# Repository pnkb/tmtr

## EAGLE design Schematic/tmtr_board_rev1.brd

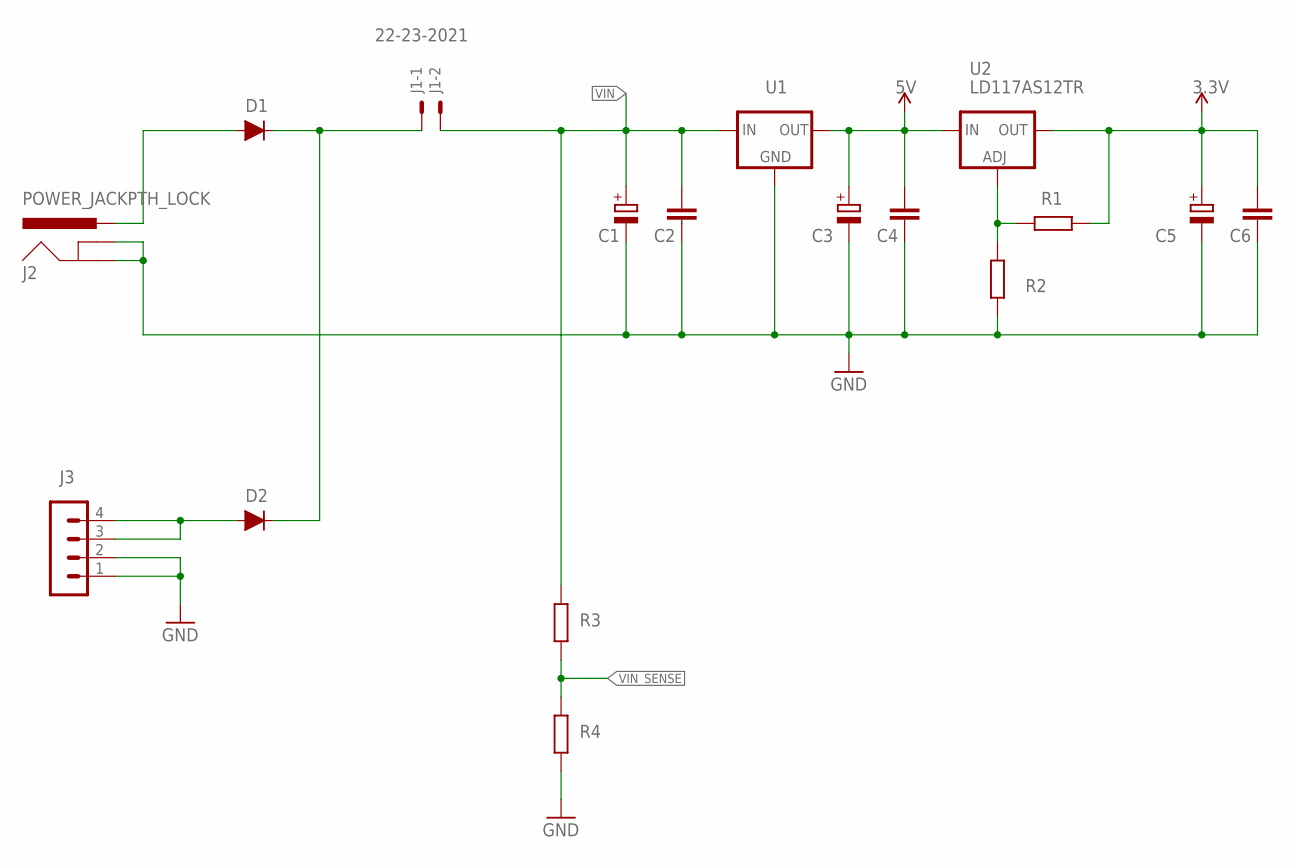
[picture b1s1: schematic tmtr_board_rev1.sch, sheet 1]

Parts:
C1: CPOL-EUE5-6; E5-6
C2, C4, C6: CAPPTH; CAP-PTH-SMALL
C3, C5: CPOL-EUE2.5-6; E2,5-6
D1, D2: D-FILL-SMB; SMB
J1: 22-23-2021
J2: POWER_JACKPTH_LOCK; POWER_JACK_PTH_LOCK
J3: MA04-1
R1, R2, R3, R4: R-EU_M0805; M0805
U1: 78XXS
U2: LD117AS12TR; SOT223

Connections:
3.3V: C5.+, C6.2, R1.2, U2.4 (OUT); also elsewhere on the board
5V: C3.+, C4.2, U1.OUT, U2.3 (IN); also elsewhere on the board
GND: C1.-, C2.1, C3.-, C4.1, C5.-, C6.1, J2.GND, J2.GNDBREAK, J3.1, J3.2, R2.2, R4.2, U1.GND; also elsewhere on the board
unnamed: D1.2 (A), J2.PWR
unnamed: D2.2 (A), J3.3, J3.4
unnamed: D1.1 (C), D2.1 (C), J1.1
unnamed: R1.1, R2.1, U2.1 (ADJ)
VIN: C1.+, C2.2, J1.2, R3.1, U1.IN
VIN_SENSE: R3.2, R4.1; also elsewhere on the board

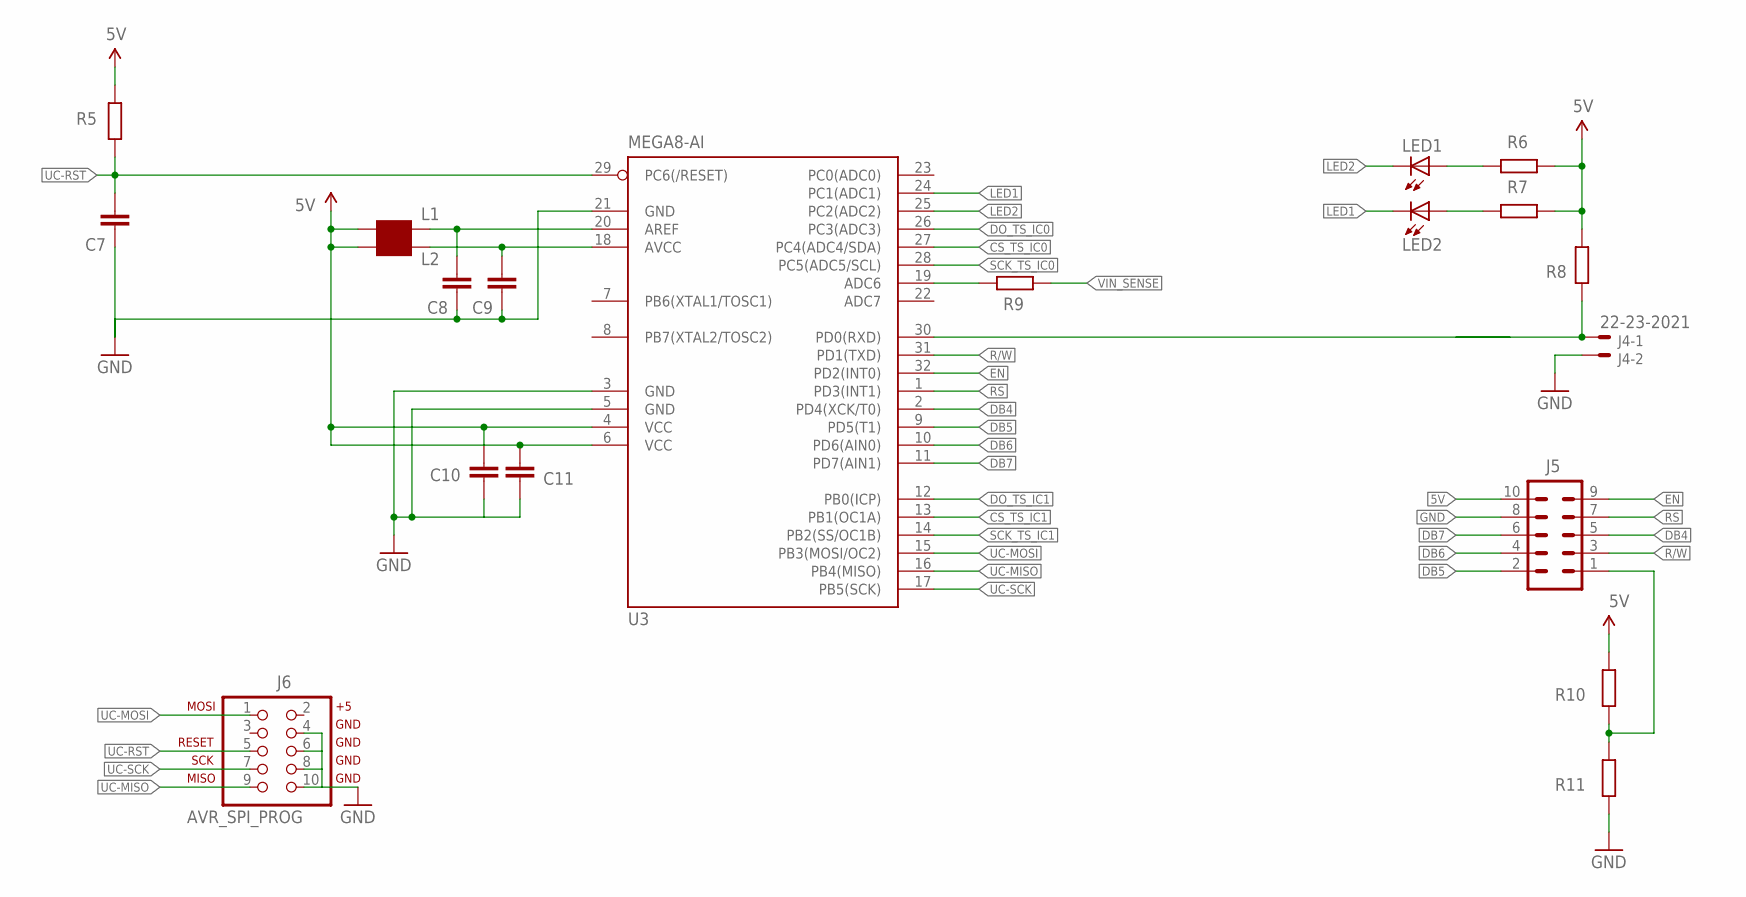
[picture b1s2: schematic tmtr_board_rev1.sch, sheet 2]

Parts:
C7, C8, C9, C10, C11: CAP0805; 0805
J4: 22-23-2021
J5: MA05-2
J6: AVR_SPI_PROG; AVR_ICSP
L1, L2: WE-CBF_0805; 0805
LED1, LED2: LEDCHIPLED_0805; CHIPLED_0805
R5: R-EU_R0805W; R0805W
R6, R7, R8, R9, R10, R11: R-EU_M0805; M0805
U3: MEGA8-AI; TQFP32-08

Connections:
5V: C10.2, C11.2, J5.10, L1.1, L2.1, R5.2, R6.1, R7.1, R8.1, R10.1, U3.4 (VCC), U3.6 (VCC); also elsewhere on the board
CS_TS_IC0: U3.27 (PC4(ADC4/SDA)); also elsewhere on the board
CS_TS_IC1: U3.13 (PB1(OC1A)); also elsewhere on the board
DB4: J5.5, U3.2 (PD4(XCK/T0))
DB5: J5.2, U3.9 (PD5(T1))
DB6: J5.4, U3.10 (PD6(AIN0))
DB7: J5.6, U3.11 (PD7(AIN1))
DO_TS_IC0: U3.26 (PC3(ADC3)); also elsewhere on the board
DO_TS_IC1: U3.12 (PB0(ICP)); also elsewhere on the board
EN: J5.9, U3.32 (PD2(INT0))
GND: C7.1, C10.1, C11.1, J4.2, J5.8, J6.4, J6.6, J6.8, J6.10, R11.2, U3.3 (GND), U3.5 (GND); also elsewhere on the board
LED1: LED2.C, U3.24 (PC1(ADC1))
LED2: LED1.C, U3.25 (PC2(ADC2))
unnamed: R9.2, U3.19 (ADC6)
unnamed: C8.2, L1.2, U3.20 (AREF)
unnamed: C9.2, L2.2, U3.18 (AVCC)
unnamed: C8.1, C9.1, U3.21 (GND)
unnamed: J4.1, R8.2, U3.30 (PD0(RXD))
unnamed: LED2.A, R7.2
unnamed: LED1.A, R6.2
unnamed: J5.1, R10.2, R11.1
R/W: J5.3, U3.31 (PD1(TXD))
RS: J5.7, U3.1 (PD3(INT1))
SCK_TS_IC0: U3.28 (PC5(ADC5/SCL)); also elsewhere on the board
SCK_TS_IC1: U3.14 (PB2(SS/OC1B)); also elsewhere on the board
UC-MISO: J6.9, U3.16 (PB4(MISO))
UC-MOSI: J6.1, U3.15 (PB3(MOSI/OC2))
UC-RST: C7.2, J6.5, R5.1, U3.29 (PC6(/RESET))
UC-SCK: J6.7, U3.17 (PB5(SCK))
VIN_SENSE: R9.1; also elsewhere on the board

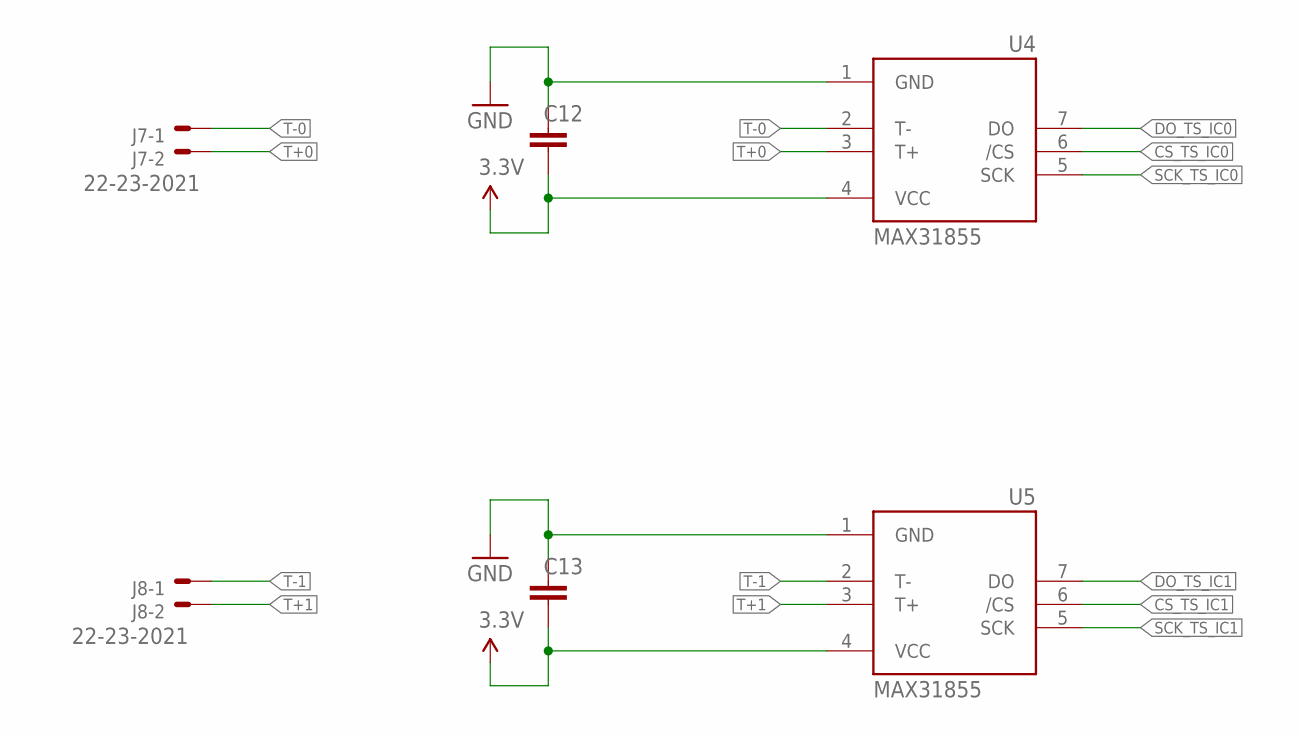
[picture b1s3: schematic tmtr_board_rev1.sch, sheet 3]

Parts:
C12, C13: CAP0805; 0805
J7, J8: 22-23-2021
U4, U5: MAX31855; SO08

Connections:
3.3V: C12.1, C13.1, U4.4 (VCC), U5.4 (VCC); also elsewhere on the board
CS_TS_IC0: U4.6 (/CS); also elsewhere on the board
CS_TS_IC1: U5.6 (/CS); also elsewhere on the board
DO_TS_IC0: U4.7 (DO); also elsewhere on the board
DO_TS_IC1: U5.7 (DO); also elsewhere on the board
GND: C12.2, C13.2, U4.1 (GND), U5.1 (GND); also elsewhere on the board
SCK_TS_IC0: U4.5 (SCK); also elsewhere on the board
SCK_TS_IC1: U5.5 (SCK); also elsewhere on the board
T+0: J7.2, U4.3 (T+)
T+1: J8.2, U5.3 (T+)
T-0: J7.1, U4.2 (T-)
T-1: J8.1, U5.2 (T-)

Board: 2 copper layers, 43 parts (0 on the bottom side), 40 nets, no tracks yet.

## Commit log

2014-12-25 :octocat: Added .gitattributes & .gitignore files
2014-12-25 New TMeter
2014-12-25 Code
2014-12-25 schematic for tmtr
